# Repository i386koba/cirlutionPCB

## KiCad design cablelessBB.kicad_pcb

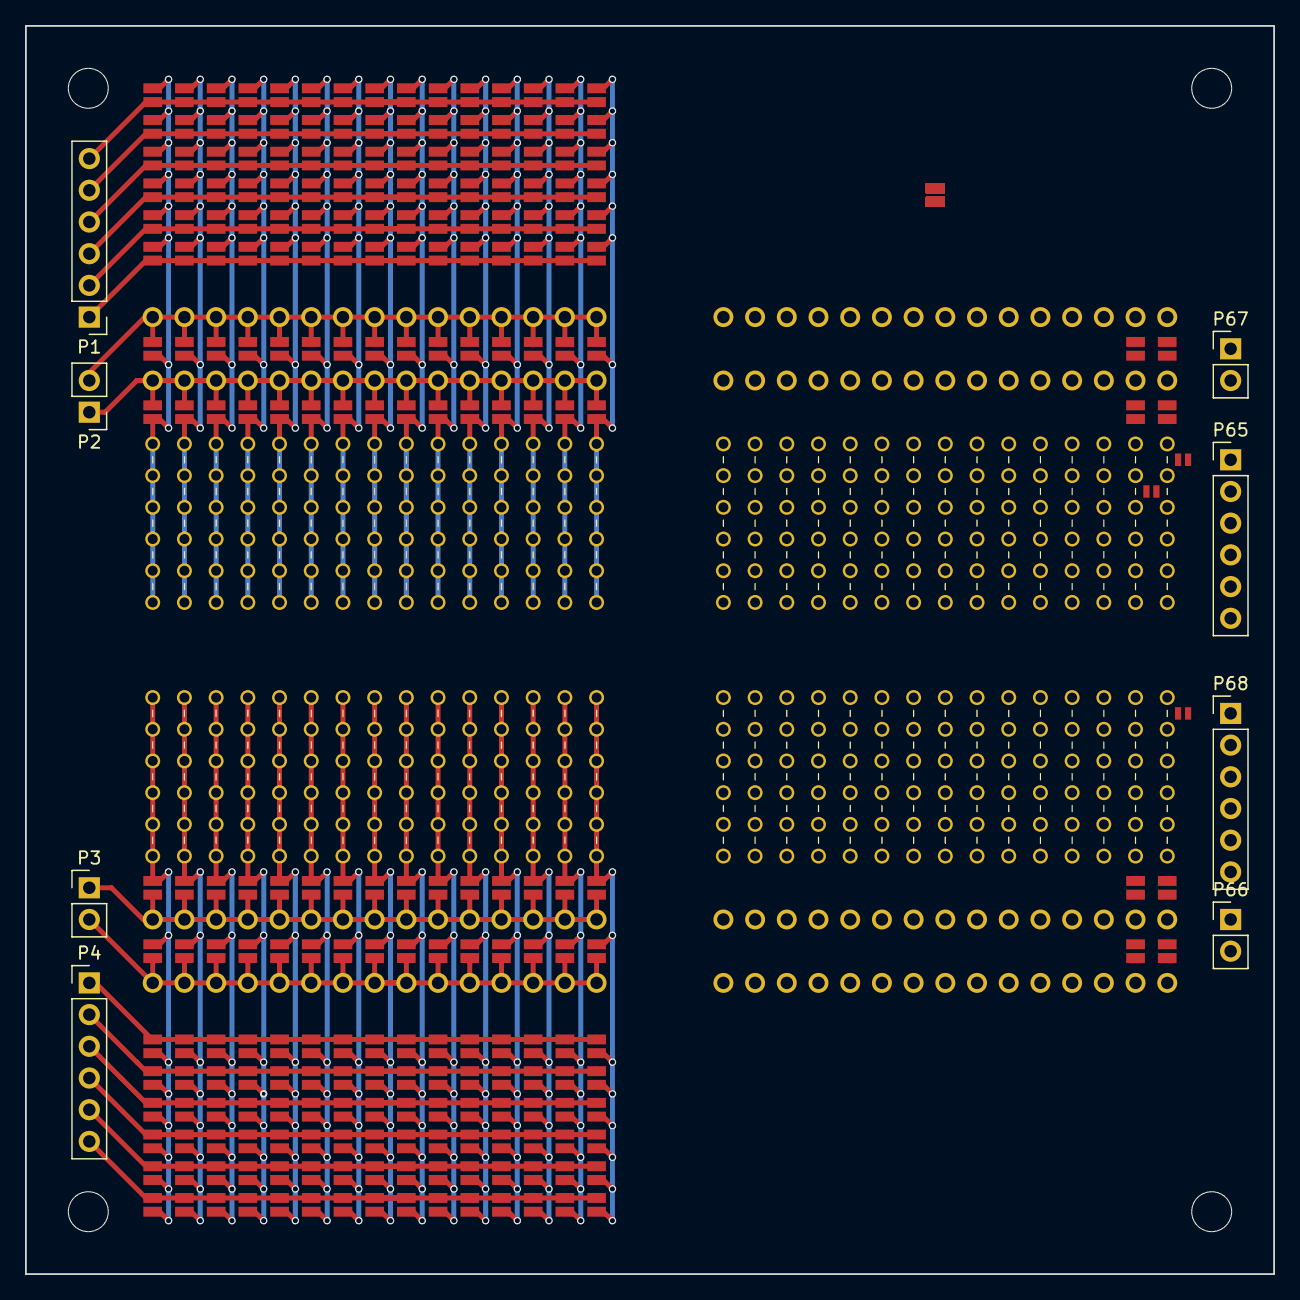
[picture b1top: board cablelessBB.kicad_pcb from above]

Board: 2 copper layers, 100.0 x 100.0 mm, 458 parts (0 on the bottom side), 86 nets.

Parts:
JP1, JP2, JP3, JP4, JP5, JP6, JP7, JP8, JP9, JP10, JP11, JP12, JP13, JP14, JP15, JP16, JP17, JP18, JP19, JP20, JP21, JP22, JP23, JP24, JP25, JP26, JP27, JP28, JP29, JP30, JP31, JP32, JP33, JP34, JP35, JP36, JP37, JP38, JP39, JP40, JP41, JP42, JP43, JP44, JP45, JP46, JP47, JP48, JP49, JP50, JP51, JP52, JP53, JP54, JP55, JP56, JP57, JP58, JP59, JP60, JP61, JP62, JP63, JP64, JP65, JP66, JP67, JP68, JP69, JP70, JP71, JP72, JP73, JP74, JP75, JP76, JP77, JP78, JP79, JP80, JP81, JP82, JP83, JP84, JP85, JP86, JP87, JP88, JP89, JP90, JP91, JP92, JP93, JP94, JP95, JP96, JP97, JP98, JP99, JP100, JP101, JP102, JP103, JP104, JP105, JP106, JP107, JP108, JP109, JP110, JP111, JP112, JP113, JP114, JP115, JP116, JP117, JP118, JP119, JP120, JP121, JP122, JP123, JP124, JP125, JP126, JP127, JP128, JP129, JP130, JP131, JP132, JP133, JP134, JP135, JP136, JP137, JP138, JP139, JP140, JP141, JP142, JP143, JP144, JP145, JP146, JP147, JP148, JP149, JP150, JP151, JP152, JP153, JP154, JP155, JP156, JP157, JP158, JP159, JP160, JP161, JP162, JP163, JP164, JP165, JP166, JP167, JP168, JP169, JP170, JP171, JP172, JP173, JP174, JP175, JP176, JP177, JP178, JP179, JP180, JP181, JP182, JP183, JP184, JP185, JP186, JP187, JP188, JP189, JP190, JP191, JP192, JP193, JP194, JP195, JP196, JP197, JP198, JP199, JP200, JP201, JP202, JP203, JP204, JP205, JP206, JP207, JP208, JP209, JP210, JP211, JP212, JP213, JP214, JP215, JP216, JP217, JP218, JP219, JP220, JP221, JP222, JP223, JP224, JP225, JP226, JP227, JP228, JP229, JP230, JP231, JP232, JP233, JP234, JP235, JP236, JP237, JP238, JP239, JP240, JP242, JP243, JP244, JP245, JP248, JP249, JP250, JP251, JP254, JP255, JP256, JP257, JP260, JP261, JP262, JP263, JP266, JP267, JP268, JP269, JP272, JP273, JP274, JP275, JP278, JP279, JP280, JP281, JP284, JP285, JP286, JP287, JP290, JP291, JP292, JP293, JP296, JP297, JP298, JP299, JP302, JP303, JP304, JP305, JP308, JP309, JP310, JP311, JP314, JP315, JP316, JP317, JP320, JP321, JP322, JP323, JP326, JP327, JP328, JP329: Jumper_NO_Small; jump
JP241, JP246, JP247, JP252, JP253, JP258, JP259, JP264, JP265, JP270, JP271, JP276, JP277, JP282, JP283, JP288, JP289, JP294, JP295, JP300, JP301, JP306, JP307, JP312, JP313, JP318, JP319, JP324, JP325, JP330: Jumper_NO_Small; j-mini
P1, P4, P65, P68: CONN_01X06; Pin_Header_Straight_1x06_Pitch2.54mm
P2, P3, P66, P67: CONN_01X02; Pin_Header_Straight_1x02_Pitch2.54mm
P5, P6, P9, P10, P13, P14, P17, P18, P21, P22, P25, P26, P29, P30, P33, P34, P37, P38, P41, P42, P45, P46, P49, P50, P53, P54, P57, P58, P61, P62, P69, P70, P73, P74, P77, P78, P81, P82, P85, P86, P89, P90, P93, P94, P97, P98, P101, P102, P105, P106, P109, P110, P113, P114, P117, P118, P121, P122, P125, P126: CONN_01X06; 6p
P7, P8, P11, P12, P15, P16, P19, P20, P23, P24, P27, P28, P31, P32, P35, P36, P39, P40, P43, P44, P47, P48, P51, P52, P55, P56, P59, P60, P63, P64, P71, P72, P75, P76, P79, P80, P83, P84, P87, P88, P91, P92, P95, P96, P99, P100, P103, P104, P107, P108, P111, P112, P115, P116, P119, P120, P123, P124, P127, P128: CONN_01X02; 2P

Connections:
GND: JP8.1, JP9.1, JP24.1, JP25.1, JP40.1, JP41.1, JP56.1, JP57.1, JP72.1, JP73.1, JP88.1, JP89.1, JP104.1, JP105.1, JP120.1, JP121.1, JP136.1, JP137.1, JP152.1, JP153.1, JP168.1, JP169.1, JP184.1, JP185.1, JP200.1, JP201.1, JP216.1, JP217.1, JP232.1, JP233.1, JP243.1, JP244.1, JP249.1, JP250.1, JP255.1, JP256.1, JP261.1, JP262.1, JP267.1, JP268.1, JP273.1, JP274.1, JP279.1, JP280.1, JP285.1, JP286.1, JP291.1, JP292.1, JP297.1, JP298.1, JP303.1, JP304.1, JP309.1, JP310.1, JP315.1, JP316.1, JP321.1, JP322.1, JP327.1, JP328.1, P2.1, P3.1, P7.2, P8.2, P11.2, P12.2, P15.2, P16.2, P19.2, P20.2, P23.2, P24.2, P27.2, P28.2, P31.2, P32.2, P35.2, P36.2, P39.2, P40.2, P43.2, P44.2, P47.2, P48.2, P51.2, P52.2, P55.2, P56.2, P59.2, P60.2, P63.2, P64.2, P66.1, P67.1, P71.2, P72.2, P75.2, P76.2, P79.2, P80.2, P83.2, P84.2, P87.2, P88.2, P91.2, P92.2, P95.2, P96.2, P99.2, P100.2, P103.2, P104.2, P107.2, P108.2, P111.2, P112.2, P115.2, P116.2, P119.2, P120.2, P123.2, P124.2, P127.2, P128.2
unnamed: JP1.1, JP17.1, JP33.1, JP49.1, JP65.1, JP81.1, JP97.1, JP113.1, JP129.1, JP145.1, JP161.1, JP177.1, JP193.1, JP209.1, JP225.1, P1.6
unnamed: JP1.2, JP2.2, JP3.2, JP4.2, JP5.2, JP6.2, JP7.2, JP8.2, P5.1, P5.2, P5.3, P5.4, P5.5, P5.6
unnamed: JP9.2, JP10.2, JP11.2, JP12.2, JP13.2, JP14.2, JP15.2, JP16.2, P6.1, P6.2, P6.3, P6.4, P6.5, P6.6
unnamed: JP17.2, JP18.2, JP19.2, JP20.2, JP21.2, JP22.2, JP23.2, JP24.2, P9.1, P9.2, P9.3, P9.4, P9.5, P9.6
unnamed: JP25.2, JP26.2, JP27.2, JP28.2, JP29.2, JP30.2, JP31.2, JP32.2, P10.1, P10.2, P10.3, P10.4, P10.5, P10.6
unnamed: JP33.2, JP34.2, JP35.2, JP36.2, JP37.2, JP38.2, JP39.2, JP40.2, P13.1, P13.2, P13.3, P13.4, P13.5, P13.6
unnamed: JP41.2, JP42.2, JP43.2, JP44.2, JP45.2, JP46.2, JP47.2, JP48.2, P14.1, P14.2, P14.3, P14.4, P14.5, P14.6
unnamed: JP49.2, JP50.2, JP51.2, JP52.2, JP53.2, JP54.2, JP55.2, JP56.2, P17.1, P17.2, P17.3, P17.4, P17.5, P17.6
unnamed: JP57.2, JP58.2, JP59.2, JP60.2, JP61.2, JP62.2, JP63.2, JP64.2, P18.1, P18.2, P18.3, P18.4, P18.5, P18.6
unnamed: JP65.2, JP66.2, JP67.2, JP68.2, JP69.2, JP70.2, JP71.2, JP72.2, P21.1, P21.2, P21.3, P21.4, P21.5, P21.6
unnamed: JP73.2, JP74.2, JP75.2, JP76.2, JP77.2, JP78.2, JP79.2, JP80.2, P22.1, P22.2, P22.3, P22.4, P22.5, P22.6
unnamed: JP81.2, JP82.2, JP83.2, JP84.2, JP85.2, JP86.2, JP87.2, JP88.2, P25.1, P25.2, P25.3, P25.4, P25.5, P25.6
unnamed: JP89.2, JP90.2, JP91.2, JP92.2, JP93.2, JP94.2, JP95.2, JP96.2, P26.1, P26.2, P26.3, P26.4, P26.5, P26.6
unnamed: JP4.1, JP20.1, JP36.1, JP52.1, JP68.1, JP84.1, JP100.1, JP116.1, JP132.1, JP148.1, JP164.1, JP180.1, JP196.1, JP212.1, JP228.1, P1.3
unnamed: JP97.2, JP98.2, JP99.2, JP100.2, JP101.2, JP102.2, JP103.2, JP104.2, P29.1, P29.2, P29.3, P29.4, P29.5, P29.6
unnamed: JP5.1, JP21.1, JP37.1, JP53.1, JP69.1, JP85.1, JP101.1, JP117.1, JP133.1, JP149.1, JP165.1, JP181.1, JP197.1, JP213.1, JP229.1, P1.2
unnamed: JP6.1, JP22.1, JP38.1, JP54.1, JP70.1, JP86.1, JP102.1, JP118.1, JP134.1, JP150.1, JP166.1, JP182.1, JP198.1, JP214.1, JP230.1, P1.1
unnamed: JP105.2, JP106.2, JP107.2, JP108.2, JP109.2, JP110.2, JP111.2, JP112.2, P30.1, P30.2, P30.3, P30.4, P30.5, P30.6
unnamed: JP11.1, JP27.1, JP43.1, JP59.1, JP75.1, JP91.1, JP107.1, JP123.1, JP139.1, JP155.1, JP171.1, JP187.1, JP203.1, JP219.1, JP235.1, P4.1
unnamed: JP12.1, JP28.1, JP44.1, JP60.1, JP76.1, JP92.1, JP108.1, JP124.1, JP140.1, JP156.1, JP172.1, JP188.1, JP204.1, JP220.1, JP236.1, P4.2
unnamed: JP13.1, JP29.1, JP45.1, JP61.1, JP77.1, JP93.1, JP109.1, JP125.1, JP141.1, JP157.1, JP173.1, JP189.1, JP205.1, JP221.1, JP237.1, P4.3
unnamed: JP14.1, JP30.1, JP46.1, JP62.1, JP78.1, JP94.1, JP110.1, JP126.1, JP142.1, JP158.1, JP174.1, JP190.1, JP206.1, JP222.1, JP238.1, P4.4
unnamed: JP15.1, JP31.1, JP47.1, JP63.1, JP79.1, JP95.1, JP111.1, JP127.1, JP143.1, JP159.1, JP175.1, JP191.1, JP207.1, JP223.1, JP239.1, P4.5
unnamed: JP16.1, JP32.1, JP48.1, JP64.1, JP80.1, JP96.1, JP112.1, JP128.1, JP144.1, JP160.1, JP176.1, JP192.1, JP208.1, JP224.1, JP240.1, P4.6
unnamed: JP113.2, JP114.2, JP115.2, JP116.2, JP117.2, JP118.2, JP119.2, JP120.2, P33.1, P33.2, P33.3, P33.4, P33.5, P33.6
unnamed: JP2.1, JP18.1, JP34.1, JP50.1, JP66.1, JP82.1, JP98.1, JP114.1, JP130.1, JP146.1, JP162.1, JP178.1, JP194.1, JP210.1, JP226.1, P1.5
unnamed: JP3.1, JP19.1, JP35.1, JP51.1, JP67.1, JP83.1, JP99.1, JP115.1, JP131.1, JP147.1, JP163.1, JP179.1, JP195.1, JP211.1, JP227.1, P1.4
unnamed: JP121.2, JP122.2, JP123.2, JP124.2, JP125.2, JP126.2, JP127.2, JP128.2, P34.1, P34.2, P34.3, P34.4, P34.5, P34.6
unnamed: JP129.2, JP130.2, JP131.2, JP132.2, JP133.2, JP134.2, JP135.2, JP136.2, P37.1, P37.2, P37.3, P37.4, P37.5, P37.6
unnamed: JP137.2, JP138.2, JP139.2, JP140.2, JP141.2, JP142.2, JP143.2, JP144.2, P38.1, P38.2, P38.3, P38.4, P38.5, P38.6
unnamed: JP145.2, JP146.2, JP147.2, JP148.2, JP149.2, JP150.2, JP151.2, JP152.2, P41.1, P41.2, P41.3, P41.4, P41.5, P41.6
unnamed: JP153.2, JP154.2, JP155.2, JP156.2, JP157.2, JP158.2, JP159.2, JP160.2, P42.1, P42.2, P42.3, P42.4, P42.5, P42.6
unnamed: JP161.2, JP162.2, JP163.2, JP164.2, JP165.2, JP166.2, JP167.2, JP168.2, P45.1, P45.2, P45.3, P45.4, P45.5, P45.6
unnamed: JP169.2, JP170.2, JP171.2, JP172.2, JP173.2, JP174.2, JP175.2, JP176.2, P46.1, P46.2, P46.3, P46.4, P46.5, P46.6
unnamed: JP177.2, JP178.2, JP179.2, JP180.2, JP181.2, JP182.2, JP183.2, JP184.2, P49.1, P49.2, P49.3, P49.4, P49.5, P49.6
unnamed: JP185.2, JP186.2, JP187.2, JP188.2, JP189.2, JP190.2, JP191.2, JP192.2, P50.1, P50.2, P50.3, P50.4, P50.5, P50.6
unnamed: JP193.2, JP194.2, JP195.2, JP196.2, JP197.2, JP198.2, JP199.2, JP200.2, P53.1, P53.2, P53.3, P53.4, P53.5, P53.6
unnamed: JP201.2, JP202.2, JP203.2, JP204.2, JP205.2, JP206.2, JP207.2, JP208.2, P54.1, P54.2, P54.3, P54.4, P54.5, P54.6
unnamed: JP209.2, JP210.2, JP211.2, JP212.2, JP213.2, JP214.2, JP215.2, JP216.2, P57.1, P57.2, P57.3, P57.4, P57.5, P57.6
unnamed: JP217.2, JP218.2, JP219.2, JP220.2, JP221.2, JP222.2, JP223.2, JP224.2, P58.1, P58.2, P58.3, P58.4, P58.5, P58.6
unnamed: JP225.2, JP226.2, JP227.2, JP228.2, JP229.2, JP230.2, JP231.2, JP232.2, P61.1, P61.2, P61.3, P61.4, P61.5, P61.6
unnamed: JP233.2, JP234.2, JP235.2, JP236.2, JP237.2, JP238.2, JP239.2, JP240.2, P62.1, P62.2, P62.3, P62.4, P62.5, P62.6
unnamed: JP241.1, JP277.1, JP313.1, P65.1
unnamed: JP241.2, JP242.2, JP243.2, P69.1, P69.2, P69.3, P69.4, P69.5, P69.6
unnamed: JP244.2, JP245.2, JP246.2, P70.1, P70.2, P70.3, P70.4, P70.5, P70.6
unnamed: JP246.1, JP282.1, JP318.1, P68.1
unnamed: JP247.1, JP283.1, JP319.1, P65.2
unnamed: JP247.2, JP248.2, JP249.2, P73.1, P73.2, P73.3, P73.4, P73.5, P73.6
unnamed: JP250.2, JP251.2, JP252.2, P74.1, P74.2, P74.3, P74.4, P74.5, P74.6
unnamed: JP252.1, JP288.1, JP324.1, P68.2
unnamed: JP253.1, JP289.1, JP325.1, P65.3
unnamed: JP253.2, JP254.2, JP255.2, P77.1, P77.2, P77.3, P77.4, P77.5, P77.6
unnamed: JP256.2, JP257.2, JP258.2, P78.1, P78.2, P78.3, P78.4, P78.5, P78.6
unnamed: JP258.1, JP294.1, JP330.1, P68.3
unnamed: JP259.1, JP295.1, P65.4
unnamed: JP259.2, JP260.2, JP261.2, P81.1, P81.2, P81.3, P81.4, P81.5, P81.6
unnamed: JP262.2, JP263.2, JP264.2, P82.1, P82.2, P82.3, P82.4, P82.5, P82.6
unnamed: JP264.1, JP300.1, P68.4
unnamed: JP265.1, JP301.1, P65.5
unnamed: JP265.2, JP266.2, JP267.2, P85.1, P85.2, P85.3, P85.4, P85.5, P85.6
unnamed: JP268.2, JP269.2, JP270.2, P86.1, P86.2, P86.3, P86.4, P86.5, P86.6
unnamed: JP270.1, JP306.1, P68.5
unnamed: JP271.1, JP307.1, P65.6
unnamed: JP271.2, JP272.2, JP273.2, P89.1, P89.2, P89.3, P89.4, P89.5, P89.6
unnamed: JP274.2, JP275.2, JP276.2, P90.1, P90.2, P90.3, P90.4, P90.5, P90.6
unnamed: JP276.1, JP312.1, P68.6
unnamed: JP277.2, JP278.2, JP279.2, P93.1, P93.2, P93.3, P93.4, P93.5, P93.6
unnamed: JP280.2, JP281.2, JP282.2, P94.1, P94.2, P94.3, P94.4, P94.5, P94.6
unnamed: JP283.2, JP284.2, JP285.2, P97.1, P97.2, P97.3, P97.4, P97.5, P97.6
unnamed: JP286.2, JP287.2, JP288.2, P98.1, P98.2, P98.3, P98.4, P98.5, P98.6
unnamed: JP289.2, JP290.2, JP291.2, P101.1, P101.2, P101.3, P101.4, P101.5, P101.6
unnamed: JP292.2, JP293.2, JP294.2, P102.1, P102.2, P102.3, P102.4, P102.5, P102.6
unnamed: JP295.2, JP296.2, JP297.2, P105.1, P105.2, P105.3, P105.4, P105.5, P105.6
unnamed: JP298.2, JP299.2, JP300.2, P106.1, P106.2, P106.3, P106.4, P106.5, P106.6
unnamed: JP301.2, JP302.2, JP303.2, P109.1, P109.2, P109.3, P109.4, P109.5, P109.6
unnamed: JP304.2, JP305.2, JP306.2, P110.1, P110.2, P110.3, P110.4, P110.5, P110.6
unnamed: JP307.2, JP308.2, JP309.2, P113.1, P113.2, P113.3, P113.4, P113.5, P113.6
unnamed: JP310.2, JP311.2, JP312.2, P114.1, P114.2, P114.3, P114.4, P114.5, P114.6
unnamed: JP313.2, JP314.2, JP315.2, P117.1, P117.2, P117.3, P117.4, P117.5, P117.6
unnamed: JP316.2, JP317.2, JP318.2, P118.1, P118.2, P118.3, P118.4, P118.5, P118.6
unnamed: JP319.2, JP320.2, JP321.2, P121.1, P121.2, P121.3, P121.4, P121.5, P121.6
unnamed: JP322.2, JP323.2, JP324.2, P122.1, P122.2, P122.3, P122.4, P122.5, P122.6
unnamed: JP325.2, JP326.2, JP327.2, P125.1, P125.2, P125.3, P125.4, P125.5, P125.6
unnamed: JP328.2, JP329.2, JP330.2, P126.1, P126.2, P126.3, P126.4, P126.5, P126.6
VCC: JP7.1, JP10.1, JP23.1, JP26.1, JP39.1, JP42.1, JP55.1, JP58.1, JP71.1, JP74.1, JP87.1, JP90.1, JP103.1, JP106.1, JP119.1, JP122.1, JP135.1, JP138.1, JP151.1, JP154.1, JP167.1, JP170.1, JP183.1, JP186.1, JP199.1, JP202.1, JP215.1, JP218.1, JP231.1, JP234.1, JP242.1, JP245.1, JP248.1, JP251.1, JP254.1, JP257.1, JP260.1, JP263.1, JP266.1, JP269.1, JP272.1, JP275.1, JP278.1, JP281.1, JP284.1, JP287.1, JP290.1, JP293.1, JP296.1, JP299.1, JP302.1, JP305.1, JP308.1, JP311.1, JP314.1, JP317.1, JP320.1, JP323.1, JP326.1, JP329.1, P2.2, P3.2, P7.1, P8.1, P11.1, P12.1, P15.1, P16.1, P19.1, P20.1, P23.1, P24.1, P27.1, P28.1, P31.1, P32.1, P35.1, P36.1, P39.1, P40.1, P43.1, P44.1, P47.1, P48.1, P51.1, P52.1, P55.1, P56.1, P59.1, P60.1, P63.1, P64.1, P66.2, P67.2, P71.1, P72.1, P75.1, P76.1, P79.1, P80.1, P83.1, P84.1, P87.1, P88.1, P91.1, P92.1, P95.1, P96.1, P99.1, P100.1, P103.1, P104.1, P107.1, P108.1, P111.1, P112.1, P115.1, P116.1, P119.1, P120.1, P123.1, P124.1, P127.1, P128.1

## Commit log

2017-02-22 add dim
2017-02-22 add test.txt
2017-02-23 del noneed file
2017-02-24 add arduinoPCB
